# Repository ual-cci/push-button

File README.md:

# Push Button Breakout Button
A breakout board for 12mm or 4.3mm tactile push buttons to be connected to a micro controller for learning environments.

The breakout features both 2.54mm and 3.5mm connections for either male or female pin headers or 3.5mm screw terminals.

Now includes a normalised and simplified Fritzing version of the part (with just the 2.54mm pads) and an Illustrator (AI) and Inkscape (SVG) file for preparing slides.

Originally designed by [Tom Lynch](https://github.com/unknowndomain) for the Creative Technology Lab at London College of Communication, version 2 updated for UAL: Creative Computing Institute.

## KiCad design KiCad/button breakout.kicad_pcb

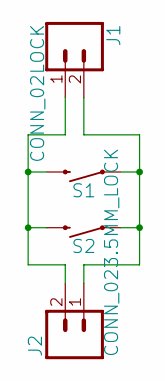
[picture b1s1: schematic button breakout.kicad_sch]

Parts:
J1: CONN_02LOCK; 1X02_LOCK
J2: CONN_023.5MM_LOCK; SCREWTERMINAL-3.5MM-2_LOCK
S1: MOMENTARY-SWITCH-SPST-PTH-12MM; TACTILE_SWITCH_PTH_12MM
S2: MOMENTARY-SWITCH-SPST-PTH-6.0MM; TACTILE_SWITCH_PTH_6.0MM

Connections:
unnamed: J1.1, J2.2, S1.3 (2), S2.3 (2)
unnamed: J1.2, J2.1, S1.1, S2.1

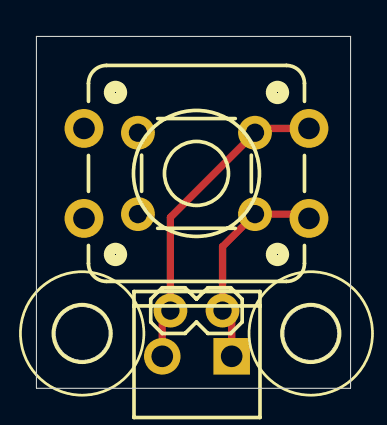
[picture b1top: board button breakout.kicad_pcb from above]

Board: 2 copper layers, 17.4 x 19.5 mm, 6 parts (0 on the bottom side), 2 nets.

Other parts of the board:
U$1, U$2: 3,0_237

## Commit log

2019-07-31 Initial commit of version 2
2019-10-06 Adds teaching resources
2025-08-21 Quick and dirty KiCAD conversion
